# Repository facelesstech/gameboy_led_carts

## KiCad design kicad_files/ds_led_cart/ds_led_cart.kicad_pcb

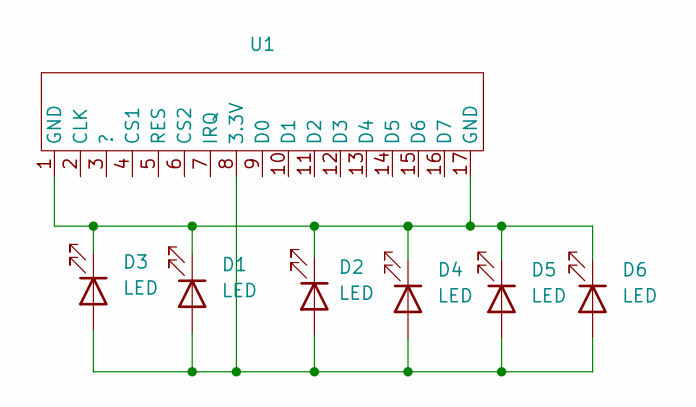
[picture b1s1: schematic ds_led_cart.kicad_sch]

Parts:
D1, D2, D3, D4, D5, D6: LED; LED_0603_1608Metric_Pad1.05x0.95mm_HandSolder
U1: ds_cart_pins

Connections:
unnamed: D1.2 (A), D2.2 (A), D3.2 (A), D4.2 (A), D5.2 (A), D6.2 (A), U1.8 (3.3V)
unnamed: D1.1 (K), D2.1 (K), D3.1 (K), D4.1 (K), D5.1 (K), D6.1 (K), U1.1 (GND), U1.17 (GND)

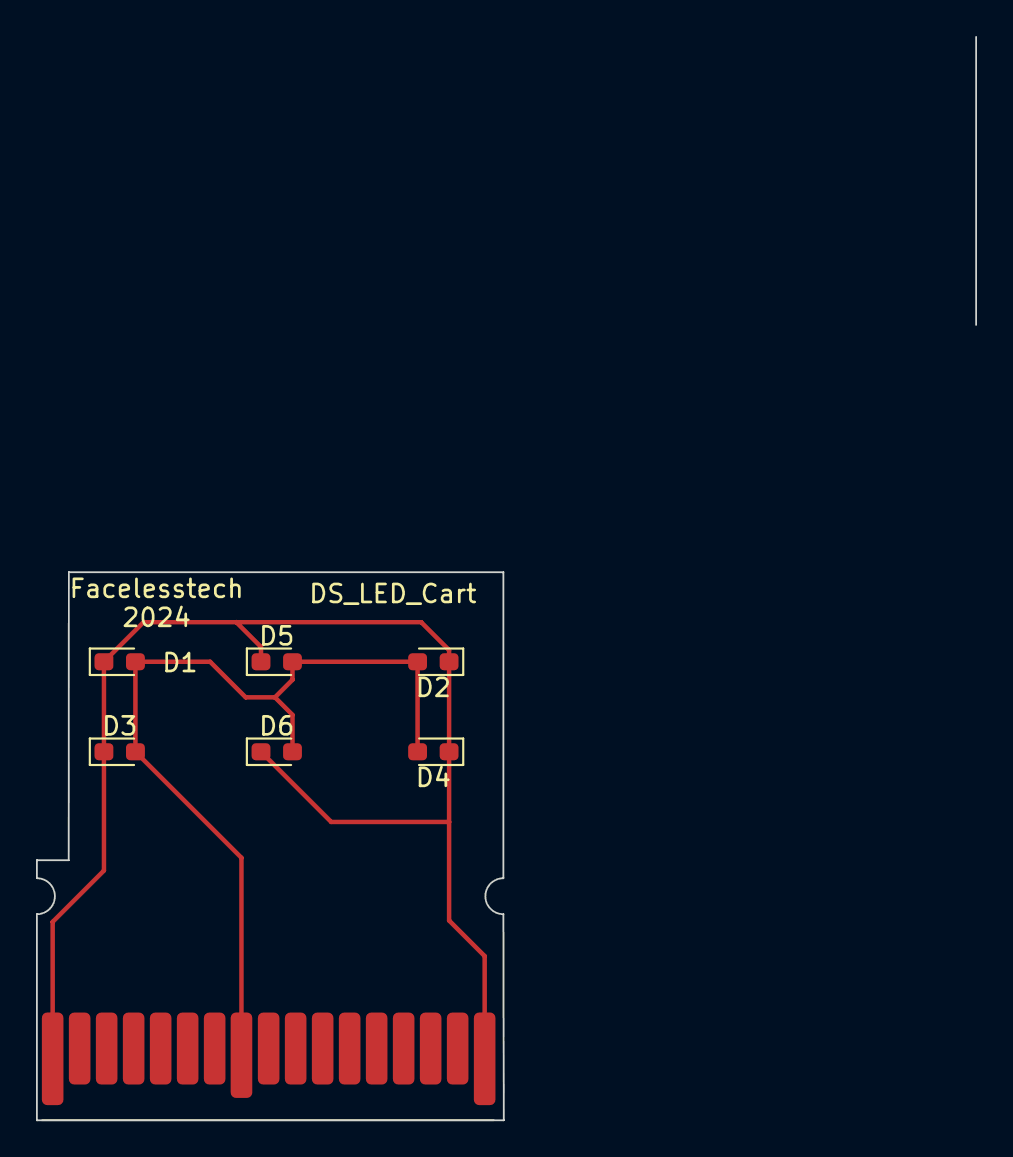
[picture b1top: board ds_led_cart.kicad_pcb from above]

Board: 2 copper layers, 52.2 x 60.2 mm, 7 parts (0 on the bottom side), 2 nets.

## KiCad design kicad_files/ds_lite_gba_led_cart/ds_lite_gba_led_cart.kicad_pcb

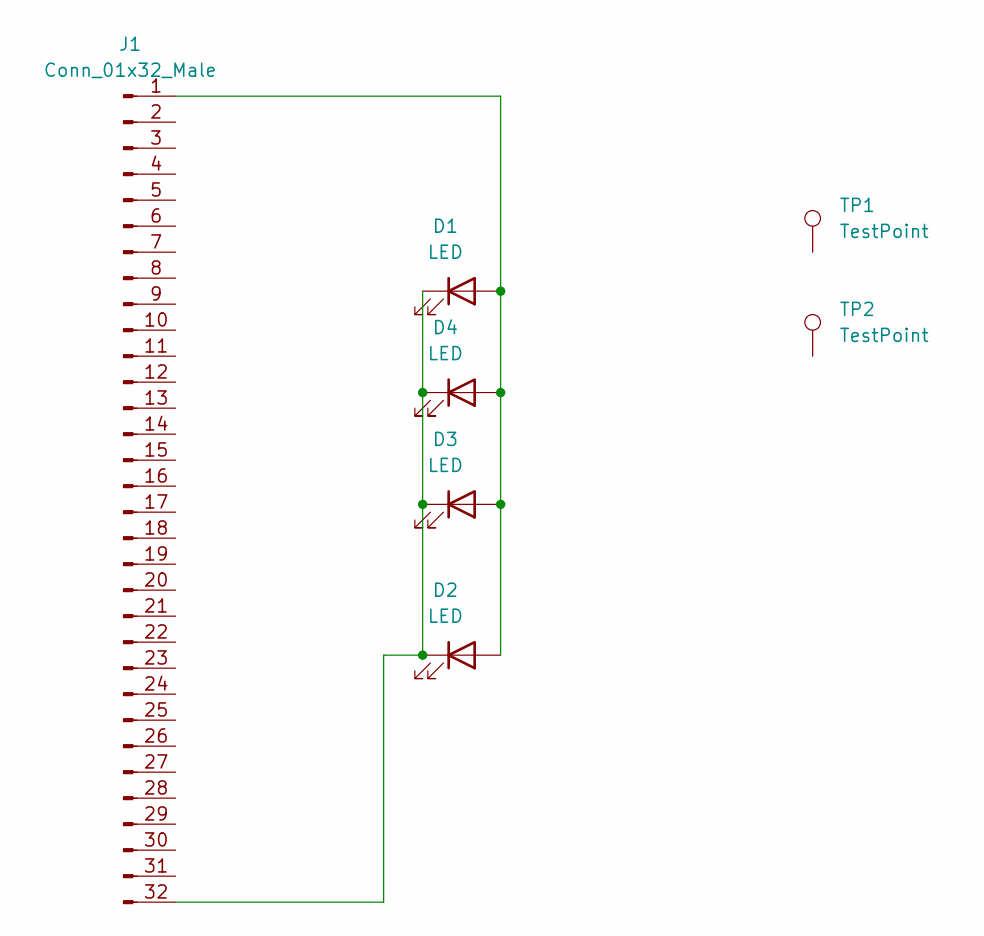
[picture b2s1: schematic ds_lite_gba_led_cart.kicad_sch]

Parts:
D1, D2, D3, D4: LED; LED_0603_1608Metric_Pad1.05x0.95mm_HandSolder
J1: Conn_01x32_Male; GBBus
TP1, TP2: TestPoint; 2mm_test_point

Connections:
unnamed: D1.2 (A), D2.2 (A), D3.2 (A), D4.2 (A), J1.1
unnamed: D1.1 (K), D2.1 (K), D3.1 (K), D4.1 (K), J1.32

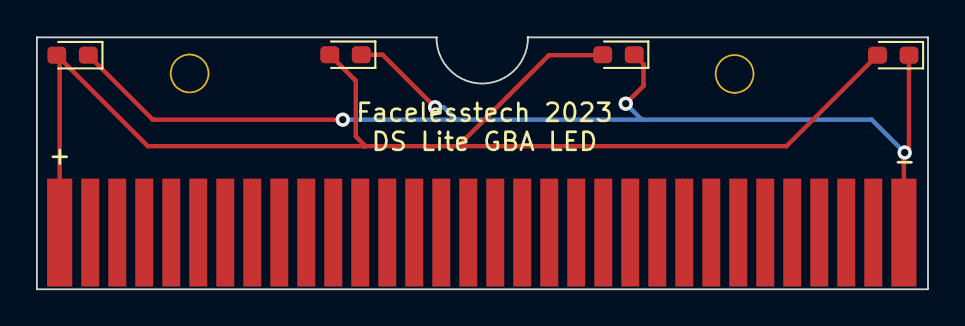
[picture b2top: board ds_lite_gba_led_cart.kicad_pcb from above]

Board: 2 copper layers, 49.5 x 14.0 mm, 7 parts (0 on the bottom side), 2 nets.

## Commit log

2024-12-22 added ds gba kicad files
2024-12-22 added ds gba 3d print files
2024-12-22 moved files
2024-12-22 added license
2024-12-22 added ds phat files
2024-12-22 added ds led files
2024-12-23 added ds led cart files
2024-12-23 uploaded a photo
2024-12-23 added 2 photos to the readme
